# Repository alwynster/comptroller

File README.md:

# comptroller

Modules to be developed:

- [ ]	AIDA64 API (read sensors)
- [ ]	MSI Afterburner API (read sensors)
- [ ] 	Razer API
- [ ] 	Asus Aura API
- [ ] 	MCU interface
- [ ] 	MCU board design
- [ ] 	Temperature Sensor
- [ ] 	RGB Strip interface (WS2812b)
- [ ] 	RGB LED interface?
- [ ] 	Custom RGB Keybaord API?

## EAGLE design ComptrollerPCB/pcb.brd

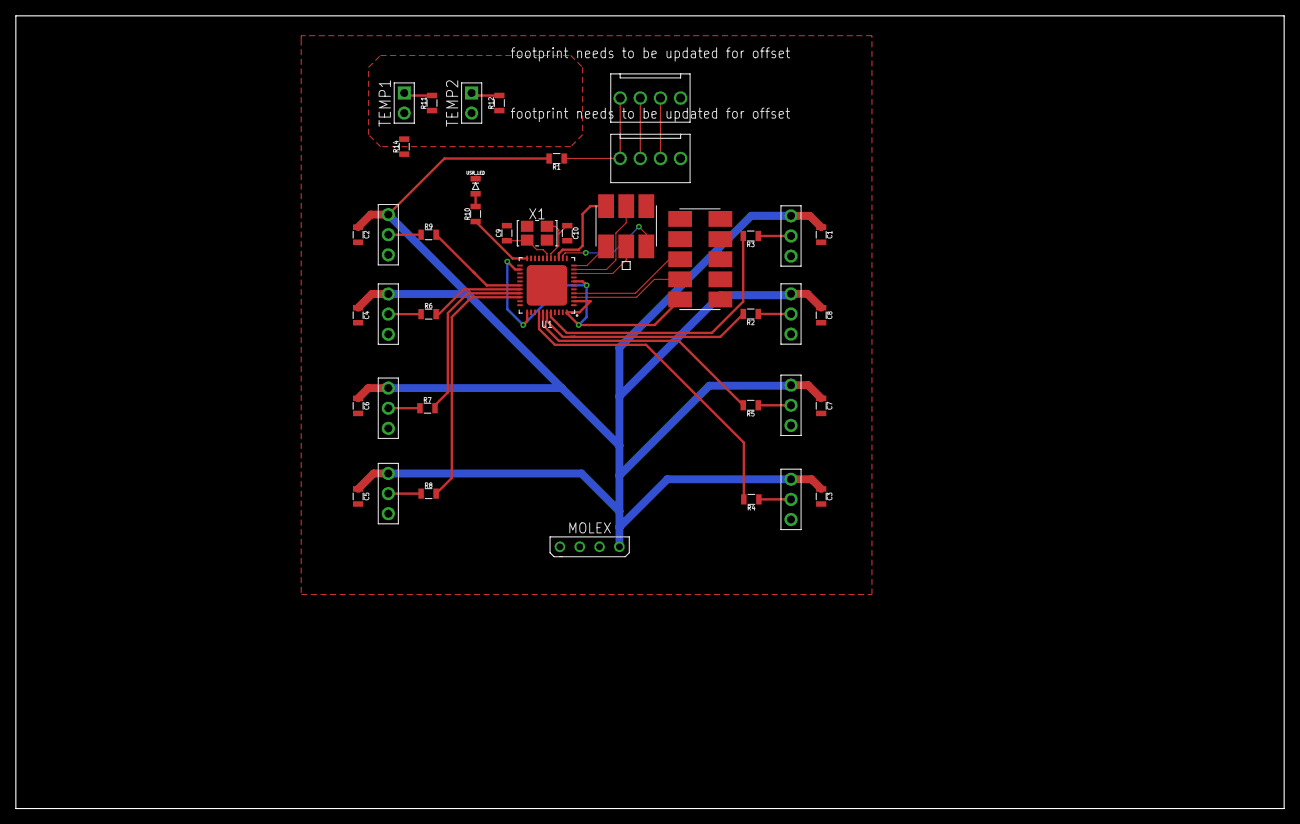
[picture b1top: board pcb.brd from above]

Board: 2 copper layers, 160.0 x 100.0 mm, 41 parts (0 on the bottom side), 35 nets.

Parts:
C1, C2, C3, C4, C5, C6, C7, C8: 470u; 0805
C9, C10: 0805
J1: FEMALE_HEADER_5X2SMT; 5X2_HEADER_SMT
J2: ISP_CONN_6PIN; 3X2_HEADER_SMT
LED_1, LED_2, LED_3, LED_4, LED_5, LED_6, LED_7, LED_8: WS2812B_3; 3X1_HEADER
MOLEX: MOLEX_POWER
PUMP: 4PIN_LED_HEADER; 4PIN_FAN_HEADER_THT
PWM_IN: 4PIN_LED_HEADER; 4PIN_FAN_HEADER_THT
R1: 3.3k; 0805
R2, R3, R4, R5, R6, R7, R8, R9: 470; 0805
R10: 330; 0805
R11, R12, R14: 0805
TEMP1, TEMP2: FEMALE_HEADER_2X1; 2X1_HEADER
U1: ATMEGA32U4; QFN44
USR_LED: 0805
X1: 16MHz; 3.2X2.5_OSC

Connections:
5V: C1.1, C2.1, C3.1, C4.1, C5.1, C6.1, C7.1, C8.1, LED_1.1, LED_2.1, LED_3.1, LED_4.1, LED_5.1, LED_6.1, LED_7.1, LED_8.1, MOLEX.4, R1.2
AGND: R14.2, TEMP1.3, TEMP2.3
GND: C1.2, C2.2, C3.2, C4.2, C5.2, C6.2, C7.2, C8.2, C9.2, C10.2, J1.7, J2.6, LED_1.5, LED_2.5, LED_3.5, LED_4.5, LED_5.5, LED_6.5, LED_7.5, LED_8.5, MOLEX.2, MOLEX.3, PUMP.4, PWM_IN.4, R14.1, U1.5, U1.15, U1.23, U1.35, U1.43, U1.45, USR_LED.2
LED_1: R3.2, U1.40
LED_2: R2.2, U1.39
LED_3: R5.2, U1.38
LED_4: R4.2, U1.37
LED_5: R8.2, U1.31
LED_6: R7.2, U1.30
LED_7: R6.2, U1.29
LED_8: R9.2, U1.28
MISO: J2.1, U1.11
MOSI: J2.4, U1.10
unnamed: LED_1.3, R2.1
unnamed: LED_2.3, R3.1
unnamed: LED_3.3, R4.1
unnamed: LED_4.3, R5.1
unnamed: LED_5.3, R6.1
unnamed: LED_6.3, R7.1
unnamed: LED_7.3, R8.1
unnamed: LED_8.3, R9.1
unnamed: R10.2, USR_LED.1
unnamed: C10.1, U1.16, X1.3
unnamed: C9.1, U1.17, X1.1
PUMP_12: PUMP.3, PWM_IN.3
PUMP_PWM: PUMP.1, PWM_IN.1, R1.1
PUMP_TACH: PUMP.2, PWM_IN.2
SCK: J2.3, U1.9
TEMP1: R11.2, TEMP1.1
TEMP2: R12.2, TEMP2.1
USB_5V: J1.10, J2.2, R11.1, R12.1, U1.2, U1.7, U1.14, U1.24, U1.34, U1.44
USB_D+: J1.8, U1.4
USB_D-: J1.9, U1.3
USR_LED: R10.1, U1.22
_RESET: J2.5, U1.13

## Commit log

2017-12-09 Initial commit with MAHM Sample added, Console client up to AIDA & MSIA measurements printout
2017-12-09 initial razer implementation that does single colour. needs to be tested outside razer env
2017-12-10 Initial design of pcb, connectors need to be updated, tracks still prelim
2017-12-13 initial mcu code to receive static colours and size, sending uart from pc. small update to pcb and LED&LEDController created on pc
2017-12-14 multiple led strings supported (tested with single led)
2017-12-19 added led animations, next step is to change the leds back to individual assignment
2017-12-23 analog additions to read temperatures
2018-01-07 added wave animation, changed communication protocol
2018-01-24 fixed buffer memory clearing and shit. only using msi afterburner now
2018-01-25 Added Asus SDK and attempt at MVP.
2018-01-27 updated pins to reservoir lights on string 3
2018-02-01 Added missing dllsfor the ASUS integration.
2018-02-01 Added a possible fix for when a razer device isn't detected.
2018-02-01 initial attempts for qmk
2018-02-01 Implemented a better (actually working) fix (I think).
2018-02-01 testing comptrollerConsole.cpp non-bin attributes
2018-02-01 hopefully fixing chinese shit
2018-02-01 turn off leds at end
2018-02-01 initial attempts ending in nothing
2018-02-01 converted to utf8
2018-02-01 Trying to fix the main file.
2018-02-01 Fixing the encoding once again.
2018-02-01 Changing line endings... for hopefully the last time.
2018-02-03 initial working version of gui with rgb synced
2018-02-04 major work on gui and config
2018-02-06 Modified the asus function to set a static color.
2018-02-06 Added the ASUS integration into master.
2018-02-25 added first version midi output
2018-02-25 got a reaction for keyboard at least
2018-02-25 fixed the static colour on keyboard
2018-03-02 integrated rtmidiin
2018-03-02 added RtMidiIn
2018-03-07 Added the continuous static update code.
2018-03-07 added fix for midi controller. Albie plox check.
2018-03-07 hotfix for tempControlList
2018-03-07 Implemented the necessary logitech stuffs.
2018-03-07 weird edits on qmk
2018-03-07 put the correct myform.h file in again
2018-03-13 small edits to try fix ryan. autostart leds, and disable static refresh
2018-03-30 small edits
2018-03-30 initial attempts...
2018-03-30 changed uart library, and general ledstring just one combo for all strings
2018-03-31 implemented handshaking, seems to work fine. needs some testing
2018-03-31 quick fix for adding qmk setting
2018-04-01 fixed (migrated to interrupt based uart rx)
2018-04-01 minor cleanup after changing to interrupt rx
2018-04-01 initial hard coded rainbow. still need to implement data switching between leds for moving rainbow
2018-04-13 fixed crash on no arduino
2018-04-13 initial razer rainbow seems to work
2018-04-13 hotfix for no led strings connected
2018-04-14 added working basic configuration. ignoring created configuration file
2018-05-11 Working motherboard lights
